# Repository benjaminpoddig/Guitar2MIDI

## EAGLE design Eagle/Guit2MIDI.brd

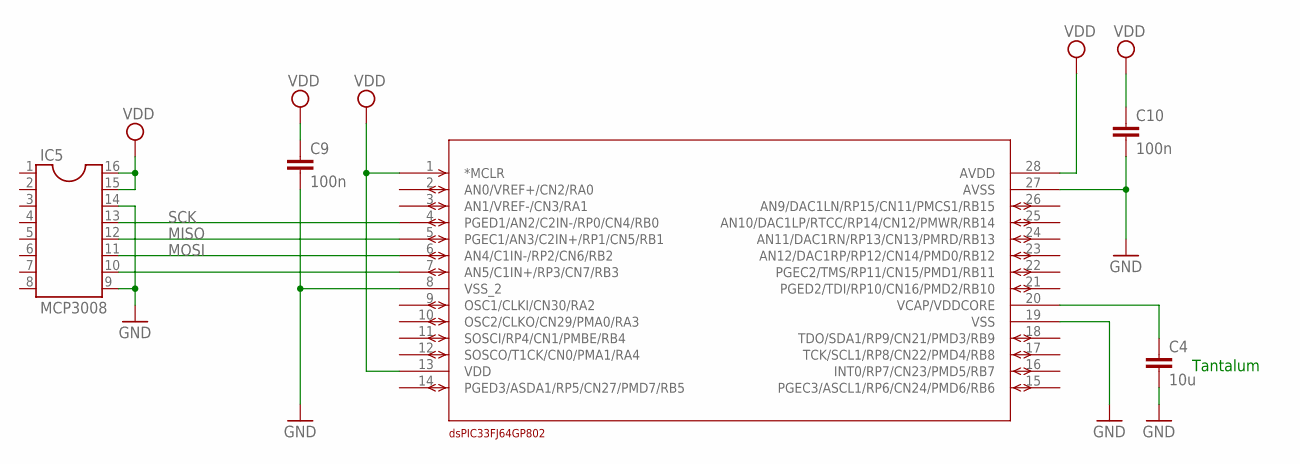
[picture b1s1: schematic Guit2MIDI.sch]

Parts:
C4: 10u; C025-030X050
C9, C10: 100n; C025-030X050
IC5: MCP3008; DIL16
U3: DSPIC33FJ64GP802; SPDIP28_300MC

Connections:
GND: C4.2, C9.2, C10.2, IC5.9, IC5.14, U3.8 (VSS_2), U3.19 (VSS), U3.27 (AVSS)
MISO: IC5.12, U3.5 (PGEC1/AN3/C2IN+/RP1/CN5/RB1)
MOSI: IC5.11, U3.6 (AN4/C1IN-/RP2/CN6/RB2)
unnamed: IC5.10, U3.7 (AN5/C1IN+/RP3/CN7/RB3)
unnamed: C4.1, U3.20 (VCAP/VDDCORE)
SCK: IC5.13, U3.4 (PGED1/AN2/C2IN-/RP0/CN4/RB0)
VDD: C9.1, C10.1, IC5.15, IC5.16, U3.1 (*MCLR), U3.13 (VDD), U3.28 (AVDD)

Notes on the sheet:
Tantalum

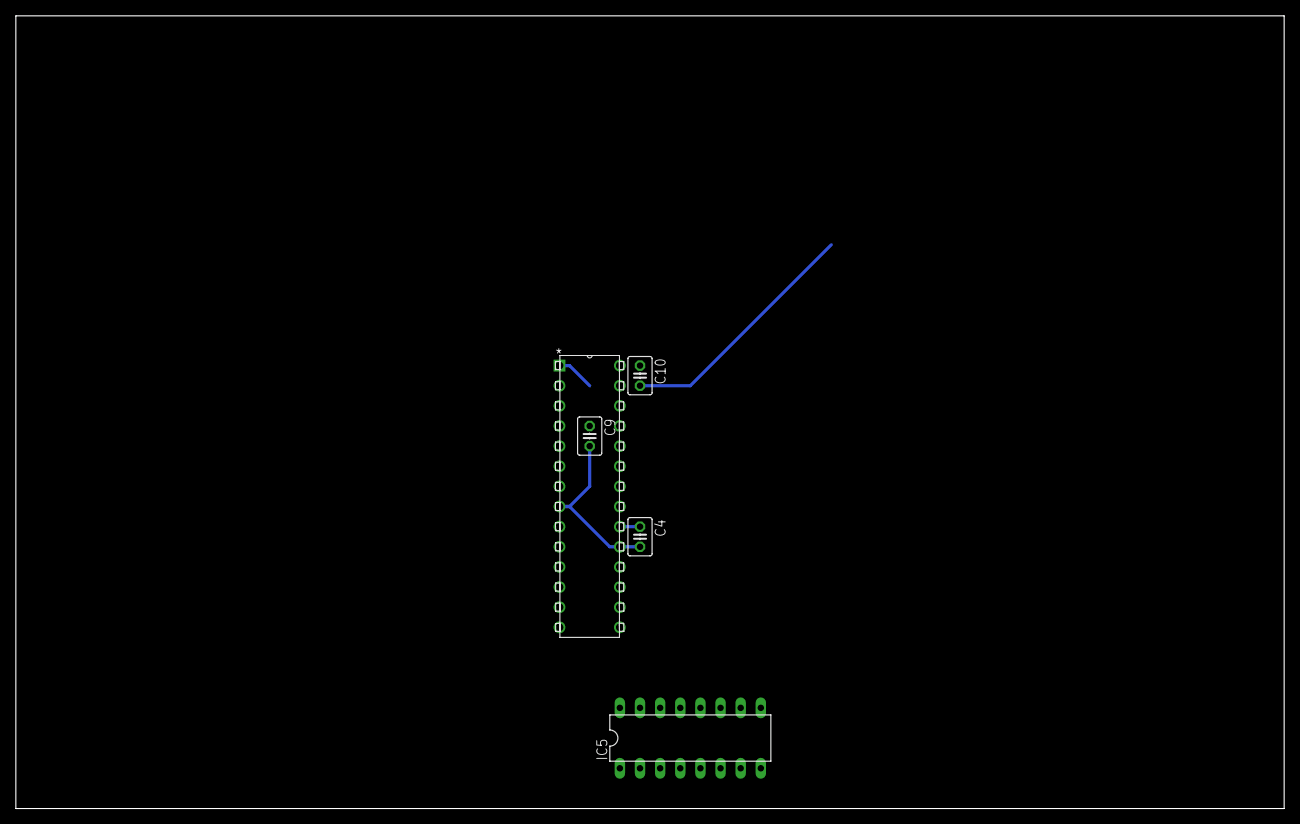
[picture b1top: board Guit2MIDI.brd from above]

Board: 2 copper layers, 160.0 x 100.0 mm, 5 parts (0 on the bottom side), 7 nets.
